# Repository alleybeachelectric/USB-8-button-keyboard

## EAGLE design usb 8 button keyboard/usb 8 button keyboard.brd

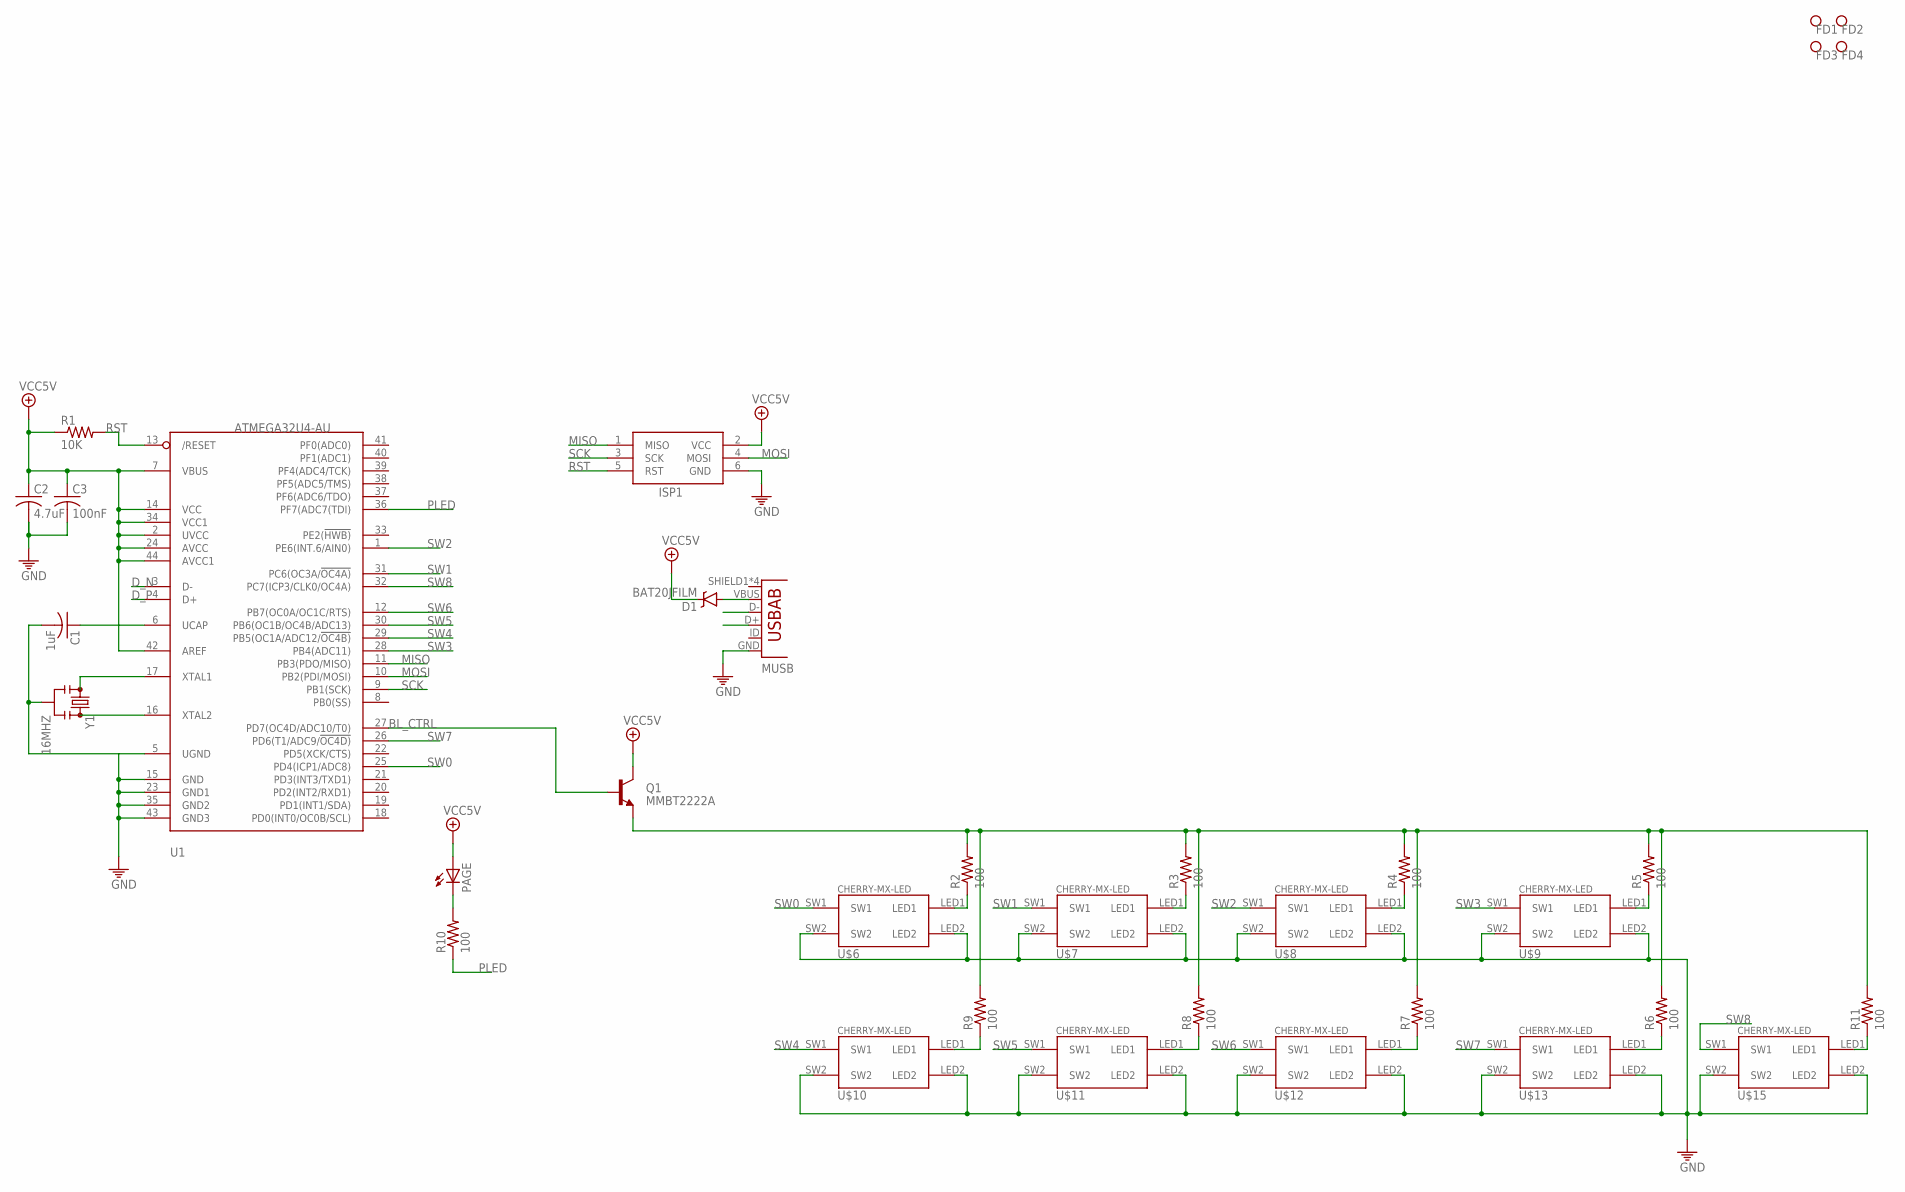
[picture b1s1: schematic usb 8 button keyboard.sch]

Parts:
C1: 1uF; C0402
C2: 4.7uF; C0402
C3: 100nF; C0402
D1: BAT20JFILM; SOD-323
FD1, FD2, FD3, FD4: FIDUCIAL; FIDUCIAL_1MM
ISP1: AVRISP-6; AVRISP
MUSB: USB-AB; USB-AB-MICRO-SMD
PAGE: LEDCHIP-LED0603; CHIP-LED0603
Q1: MMBT2222A; SOT23-3
R1: 10K; R0402
R2, R3, R4, R5, R6, R7, R8, R9, R10, R11: 100; R0402
U1: ATMEGA32U4-AU; TQFP44
U$6, U$7, U$8, U$9, U$10, U$11, U$12, U$13, U$15: CHERRY-MX-LED
Y1: 16MHZ; RESONATOR-SMD

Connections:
BL: Q1.2 (E), R2.2, R3.2, R4.2, R5.2, R6.2, R7.2, R8.2, R9.2, R11.2
BL_CTRL: Q1.1 (B), U1.27 (PD7(OC4D/ADC10/T0))
D_N: MUSB.D-, U1.3 (D-)
D_P: MUSB.D+, U1.4 (D+)
GND: C1.2, C2.2, C3.2, ISP1.6 (GND), MUSB.GND, U1.5 (UGND), U1.15 (GND), U1.23 (GND1), U1.35 (GND2), U1.43 (GND3), U$6.LED2, U$6.SW2, U$7.LED2, U$7.SW2, U$8.LED2, U$8.SW2, U$9.LED2, U$9.SW2, U$10.LED2, U$10.SW2, U$11.LED2, U$11.SW2, U$12.LED2, U$12.SW2, U$13.LED2, U$13.SW2, U$15.LED2, U$15.SW2, Y1.2
MISO: ISP1.1 (MISO), U1.11 (PB3(PDO/MISO))
MOSI: ISP1.4 (MOSI), U1.10 (PB2(PDI/MOSI))
unnamed: D1.A, MUSB.VBUS
unnamed: PAGE.C, R10.2
unnamed: R11.1, U$15.LED1
unnamed: R2.1, U$6.LED1
unnamed: U1.16 (XTAL2), Y1.3
unnamed: U1.17 (XTAL1), Y1.1
unnamed: C1.1, U1.6 (UCAP)
unnamed: R3.1, U$7.LED1
unnamed: R4.1, U$8.LED1
unnamed: R5.1, U$9.LED1
unnamed: R6.1, U$13.LED1
unnamed: R7.1, U$12.LED1
unnamed: R8.1, U$11.LED1
unnamed: R9.1, U$10.LED1
PLED: R10.1, U1.36 (PF7(ADC7(TDI))
RST: ISP1.5 (RST), R1.2, U1.13 (/RESET)
SCK: ISP1.3 (SCK), U1.9 (PB1(SCK))
SW0: U1.25 (PD4(ICP1/ADC8)), U$6.SW1
SW1: U1.31 (PC6(OC3A/!OC4A)), U$7.SW1
SW2: U1.1 (PE6(INT.6/AIN0)), U$8.SW1
SW3: U1.28 (PB4(ADC11)), U$9.SW1
SW4: U1.29 (PB5(OC1A/ADC12/!OC4B)), U$10.SW1
SW5: U1.30 (PB6(OC1B/OC4B/ADC13)), U$11.SW1
SW6: U1.12 (PB7(OC0A/OC1C/RTS)), U$12.SW1
SW7: U1.26 (PD6(T1/ADC9/!OC4D)), U$13.SW1
SW8: U1.32 (PC7(ICP3/CLK0/OC4A)), U$15.SW1
VCC5V: C2.1, C3.1, D1.C, ISP1.2 (VCC), PAGE.A, Q1.3 (C), R1.1, U1.2 (UVCC), U1.7 (VBUS), U1.14 (VCC), U1.24 (AVCC), U1.34 (VCC1), U1.42 (AREF), U1.44 (AVCC1)

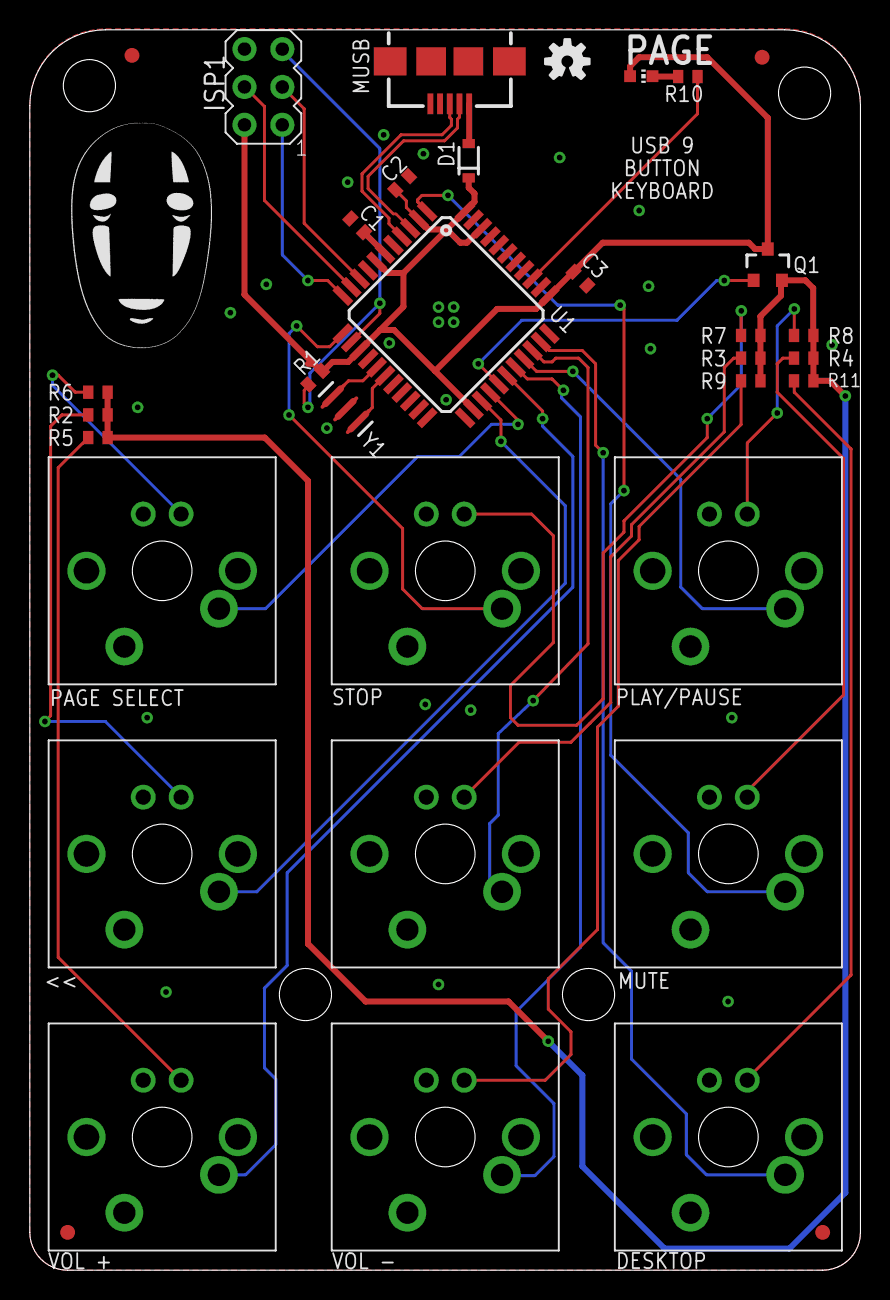
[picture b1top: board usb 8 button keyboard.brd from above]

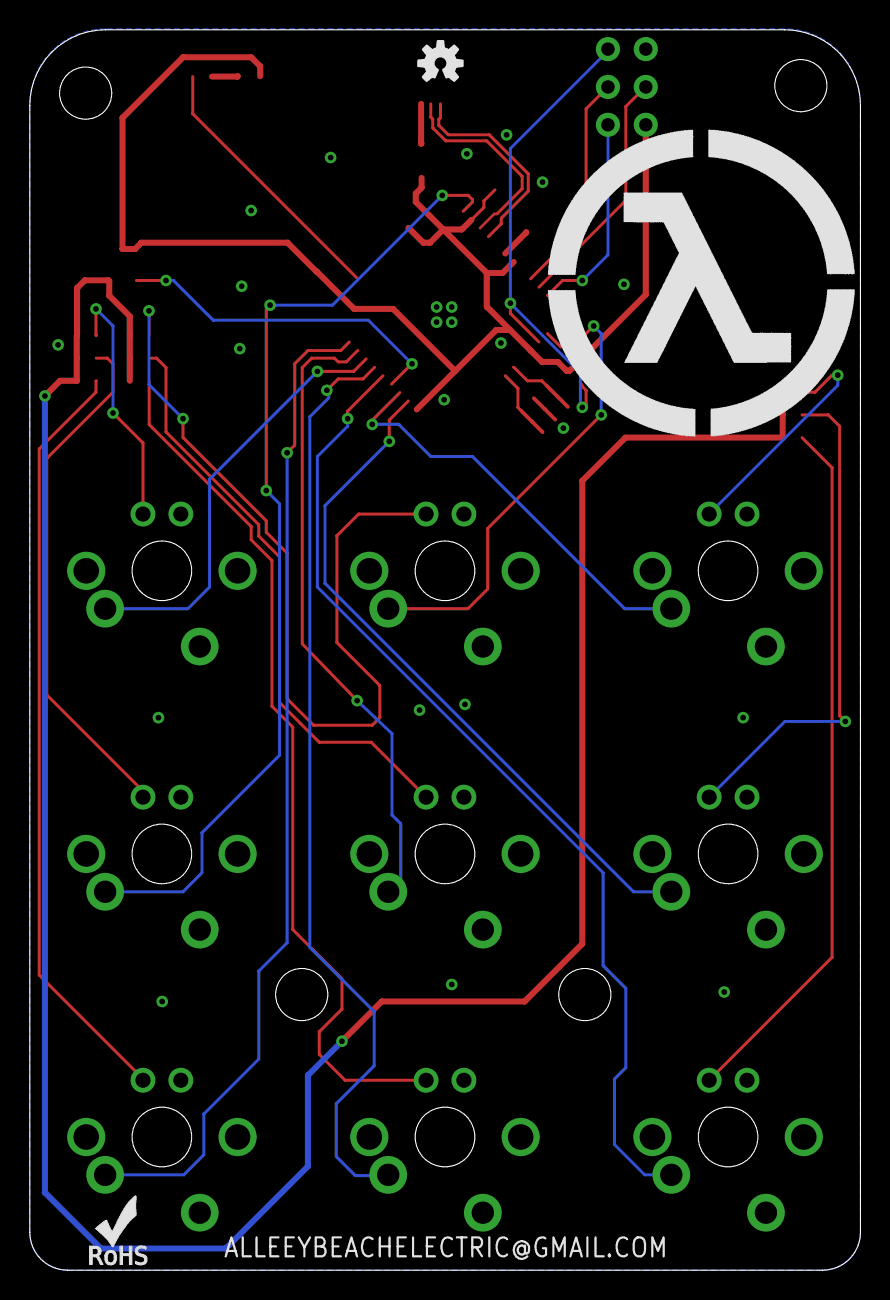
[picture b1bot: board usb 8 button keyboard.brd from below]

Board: 4 copper layers, 55.8 x 83.2 mm, 37 parts (2 on the bottom side), 34 nets.

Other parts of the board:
U$1, U$16: OSHW-LOGO-S
U$17: ROHS_LOGO_0.18_IN

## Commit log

2016-09-07 add pcb with proper key spacing.
2016-09-14 should be the right size now.
2016-09-26 added sample code.
2016-10-14 adding stuffz
2016-10-14 intigrated Media function, along with use of AHK.
2016-11-03 new version. 9 buttons!
2016-11-12 cleaned up silk, rotated mx switches so LED's are on top, cleaned up some redundent ass routing. added ROHS cert logo.
2016-11-21 added 1-0. this counts 0 to 1 with the page, so it knows what page its on.
2016-11-22 adding stuff.
2016-11-30 added better code.
2016-12-30 added plate gcode. added pwm led support.

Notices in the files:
parts and their libraries:
SparkFun-FreqCtrl: Licensing: Creative Commons ShareAlike 4.0 International - https://creativecommons.org/licenses/by-sa/4.0
